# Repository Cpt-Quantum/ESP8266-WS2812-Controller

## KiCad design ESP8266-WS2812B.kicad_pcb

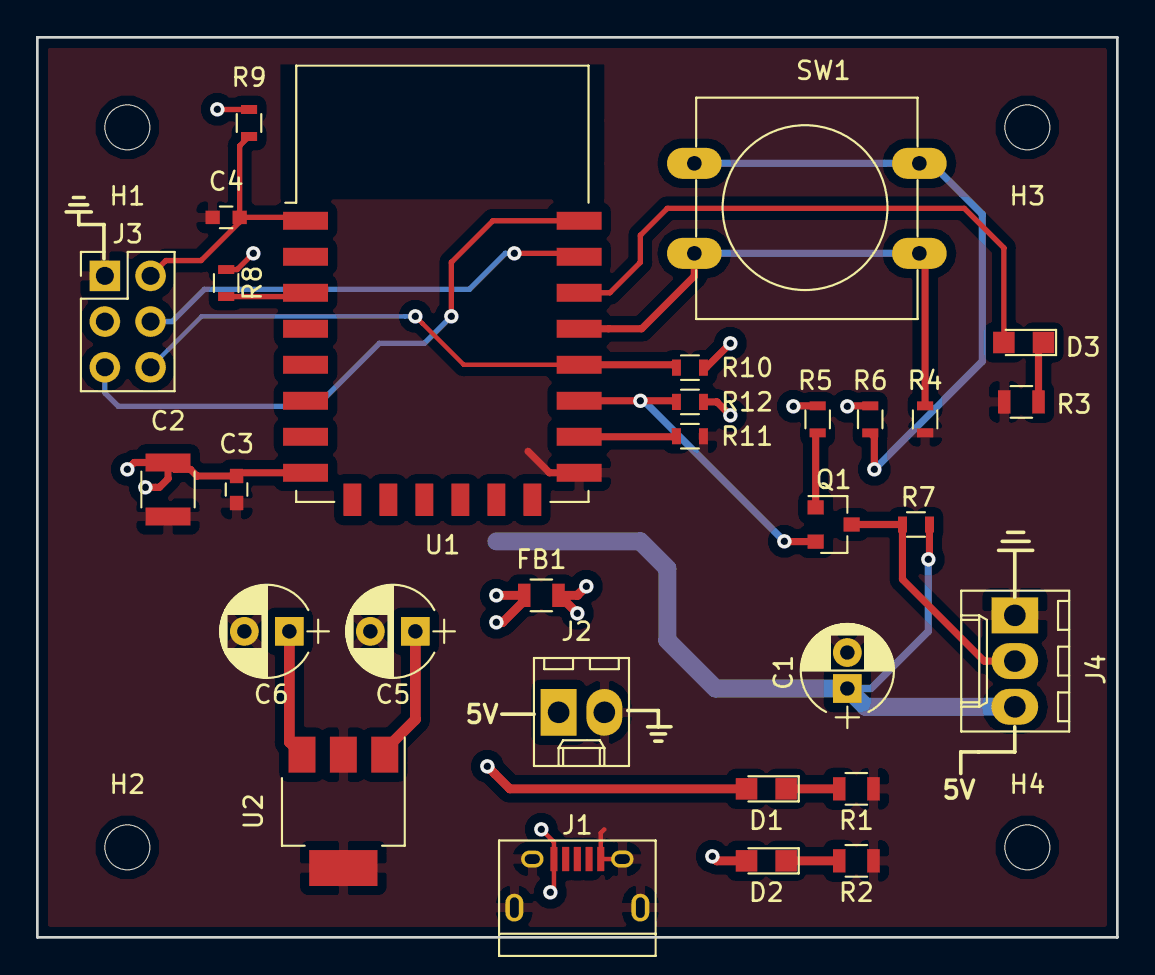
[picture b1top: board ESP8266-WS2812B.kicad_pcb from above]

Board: 2 copper layers, 60.0 x 50.0 mm, 34 parts (0 on the bottom side), 19 nets.

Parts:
C1: 22uF; CP_Radial_D5.0mm_P2.00mm
C2: 100uF; C_1210
C3, C4: 0.1uF; C_0603
C5, C6: 4.7uF; CP_Radial_D5.0mm_P2.50mm
D1, D2, D3: LED; LED_0805
FB1: Ferrite_Bead; L_0805
H1, H2, H3, H4: MountingHole; MountingHole_2.5mm
J1: USB_B_Micro; USB_Micro-B
J2: Alternate_Power_Input; Molex_KK-6410-02_02x2.54mm_Straight
J3: Conn_02x03_Odd_Even; Pin_Header_Straight_2x03_Pitch2.54mm
J4: Conn_01x03; Molex_KK-6410-03_03x2.54mm_Straight
Q1: Q_NPN_BEC; SOT-23
R1: 680R; R_0805
R2, R3: 430R; R_0805
R4, R6, R7, R8, R9, R10, R11, R12: 10kR; R_0603
R5: 3.3kR; R_0603
SW1: SW_Push; SW_PUSH-12mm
U1: ESP-12F; ESP-12E
U2: AP2114HA-3.3; SOT-223

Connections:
+3V3: C2.1, C3.1, C6.1, D2.2, R5.1, R6.1, R8.1, R9.1, R10.1, R12.1, U1.8, U2.3
+5V: C1.1, C5.1, D1.2, FB1.1, J4.3, R7.2, U2.1
/3.3V_LED_A: D2.1, R2.1
/5V_Input: FB1.2, J1.1, J2.1
/5V_LED_A: D1.1, R1.1
/Button_Open_Side: R6.2, SW1.2
/DATA: J4.2, Q1.3, R7.1
/ESP8266/EN: R8.2, U1.3
/ESP8266/GPIO2: Q1.2, R12.2, U1.17
/ESP8266/GPIO4: R4.1, SW1.1, U1.19
/ESP8266/GPIO5: D3.2, U1.20
/ESP8266/GPIO15: R11.1, U1.16
/GPIO0: J3.6, R10.2, U1.18
/Level_Shift_Base: Q1.1, R5.2
/RXD: J3.4, U1.21
/TXD: J3.5, U1.22
/User_LED_A: D3.1, R3.1
/~RST: C4.1, J3.2, R9.2, U1.1
GND: C1.2, C2.2, C3.2, C4.2, C5.2, C6.2, J1.5, J1.6, J2.2, J3.1, J4.1, R1.2, R2.2, R3.2, R4.2, R11.2, U1.15, U2.2, U2.4

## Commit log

2018-10-14 Initial work on schematic.
2018-10-22 Moved the ESP8266 module and it's programming circuitry to it's own hierarchical sheet. Also added user and power LEDs.
2018-10-29 Removed auto-programming circuit to conserve space, this will need it's own separate board.
2018-10-31 Moved 3.3V regulator to its own sheet for easier future resuse and tidied up/named some nets.
2018-11-02 Added a user button for general use
2018-11-04 Annotated schematic and added footprints.
2018-11-05 Fixed library symbol for the 3.3V regulator. Also added correct footprint path for the ESP-12E.
2018-11-05 Generated netlist, added mounting holes and completed rough component placement on PCB.
2018-11-06 Arranged components and drawn PCB outline
2018-11-06 Added copper fill/no fill zones and finished first pass of connecting all nets.
2018-11-08 Added pdf of schematic.
2018-11-13 Generated gerbers and allowed GND copper flow to flow under the ESP module.
2018-11-13 Added PCB/author information on bottom silkscreen layer and added some connector information on top silkscreen layer.
